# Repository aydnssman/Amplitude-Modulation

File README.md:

# Amplitude-Modulation
Schematic and PCB were drawn using Autodesk Eagle software. The whole system has been tested and working.

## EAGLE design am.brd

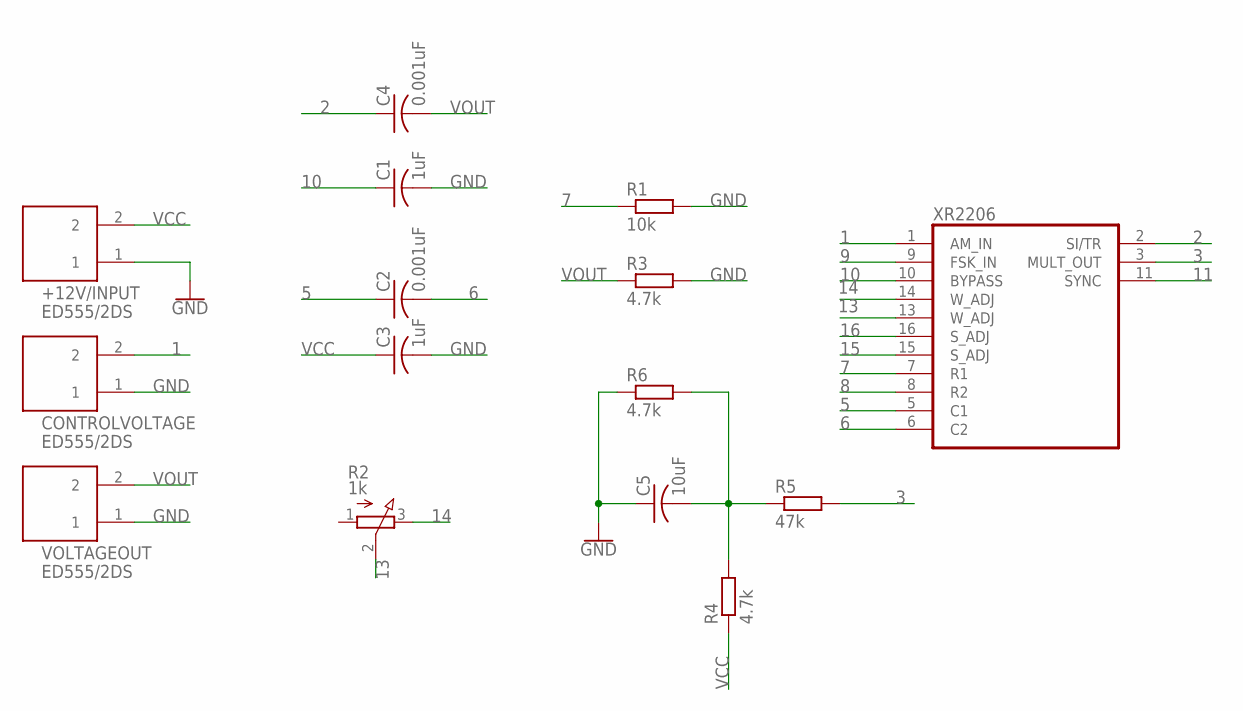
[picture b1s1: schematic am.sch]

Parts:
+12V/INPUT: ED555/2DS
C1, C3: 1uF; C050-030X075
C2, C4: 0.001uF; C050-030X075
C5: 10uF; C050-030X075
CONTROLVOLTAGE: ED555/2DS
R1: 10k; 0207/10
R2: 1k; 3RP/1610N
R3, R4, R6: 4.7k; 0207/10
R5: 47k; 0207/10
VOLTAGEOUT: ED555/2DS
XR2206: XR-2206; DIL16

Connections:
1: CONTROLVOLTAGE.2, XR2206.1 (AM_IN)
2: C4.1, XR2206.2 (SI/TR)
3: R5.2, XR2206.3 (MULT_OUT)
5: C2.1, XR2206.5 (C1)
6: C2.2, XR2206.6 (C2)
7: R1.1, XR2206.7 (R1)
8: XR2206.8 (R2)
9: XR2206.9 (FSK_IN)
10: C1.1, XR2206.10 (BYPASS)
11: XR2206.11 (SYNC)
13: R2.2 (S), XR2206.13 (W_ADJ)
14: R2.3 (E), XR2206.14 (W_ADJ)
15: XR2206.15 (S_ADJ)
16: XR2206.16 (S_ADJ)
GND: +12V/INPUT.1, C1.2, C3.2, C5.1, CONTROLVOLTAGE.1, R1.2, R3.2, R6.1, VOLTAGEOUT.1, XR2206.12 (GND)
unnamed: C5.2, R4.2, R5.1, R6.2
VCC: +12V/INPUT.2, C3.1, R4.1, XR2206.4 (VCC)
VOUT: C4.2, R3.1, VOLTAGEOUT.2

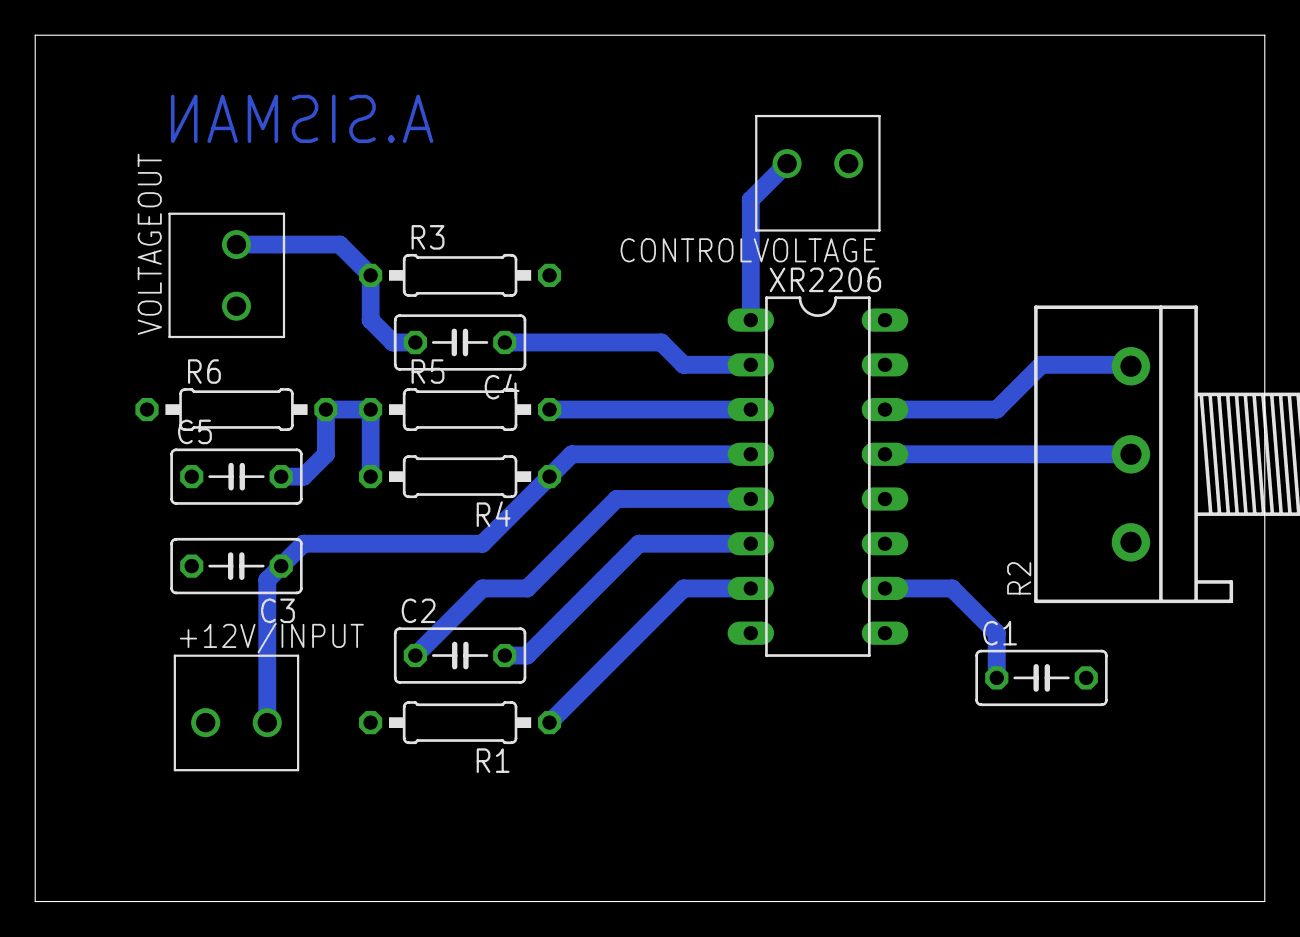
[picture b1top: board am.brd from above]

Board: 2 copper layers, 69.8 x 49.2 mm, 15 parts (0 on the bottom side), 13 nets.

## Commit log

2019-12-16 Amplitude Modulation
2019-12-18 Added datasheet

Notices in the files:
parts and their libraries:
SparkFun-PowerSymbols: Licensing: Creative Commons ShareAlike 4.0 International - https://creativecommons.org/licenses/by-sa/4.0
